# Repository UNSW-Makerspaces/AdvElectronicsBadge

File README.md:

# Arduino-Pico

Raspberry Pi Pico Arduino core, for all RP2040 boards

This is a port of the RP2040 (Raspberry Pi Pico processor) to the Arduino ecosystem. It uses the bare Raspberry Pi Pico SDK and a custom GCC 10.3/Newlib 4.0 toolchain.

# Documentation
See https://arduino-pico.readthedocs.io/en/latest/ along with the examples for more detailed usage information.

# Contributing
Read the [Contributing Guide](https://github.com/earlephilhower/arduino-pico/blob/master/docs/contrib.rst) for more information on submitting pull requests and porting libraries or sketches to this core.

# Supported Boards
* Raspberry Pi Pico
* Raspberry Pi Pico W
* UNSW Makerspaces PicoGamePad
* 0xCB Helios
* Adafruit Feather RP2040
* Adafruit Feather RP2040 SCORPIO
* Adafruit ItsyBitsy RP2040
* Adafruit KB2040
* Adafruit Macropad RP2040
* Adafruit QTPy RP2040
* Adafruit STEMMA Friend RP2040
* Adafruit Trinkey RP2040 QT
* Arduino Nano RP2040 Connect
* BridgeTek IDM2040-7A
* Cytron Maker Pi RP2040
* Cytron Maker Nano RP2040
* DatanoiseTV PicoADK+
* DeRuiLab FlyBoard2040 Core
* DFRobot Beetle RP2040
* ElectronicCats Hunter Cat NFC
* ExtremeElectronics RC2040
* Invector Labs Challenger RP2040 WiFi
* Invector Labs Challenger RP2040 WiFi/BLE
* Invector Labs Challenger NB RP2040 WiFi
* Invector Labs Challenger RP2040 LTE
* Invector Labs Challenger RP2040 LoRa
* Invector Labs Challenger RP2040 SubGHz
* Invector Labs Challenger RP2040 SD/RTC
* Invector Labs RPICO32
* Melopero Cookie RP2040
* Melopero Shake RP2040
* nullbits Bit-C PRO
* Pimoroni PGA2040
* Seeed XIAO RP2040
* Solder Party RP2040 Stamp
* SparkFun ProMicro RP2040
* SparkFun Thing Plus RP2040
* uPesy RP2040 DevKit
* VCC-GND YD-RP2040
* Viyalab Mizu RP2040
* Waveshare RP2040 Zero
* Waveshare RP2040 One
* Waveshare RP2040 Plus
* Waveshare RP2040 LCD 0.96
* Waveshare RP2040 LCD 1.28
* WIZnet W5100S-EVB-Pico
* WIZnet W5500-EVB-Pico
* WIZnet WizFi360-EVB-Pico
* Generic (configurable flash, I/O pins)

# Installing via Arduino Boards Manager
**Windows Users**: Please do not use the Windows Store version of the actual Arduino application
because it has issues detecting attached Pico boards.  Use the "Windows ZIP" or plain "Windows"
executable (EXE)  download direct from https://arduino.cc. and allow it to install any device
drivers it suggests.  Otherwise the Pico board may not be detected.  Also, if trying out the
2.0 beta Arduino please install the release 1.8 version beforehand to ensure needed device drivers
are present.  (See #20 for more details.)

Open up the Arduino IDE and go to File->Preferences.

In the dialog that pops up, enter the following URL in the "Additional Boards Manager URLs" field:

https://github.com/earlephilhower/arduino-pico/releases/download/global/package_rp2040_index.json

Hit OK to close the dialog.

Go to Tools->Boards->Board Manager in the IDE

Type "pico" in the search box and select "Add":

# Installing via GIT
To install via GIT (for latest and greatest versions):
````
mkdir -p ~/Arduino/hardware/pico
git clone https://github.com/earlephilhower/arduino-pico.git ~/Arduino/hardware/pico/rp2040
cd ~/Arduino/hardware/pico/rp2040
git submodule update --init
cd pico-sdk
git submodule update --init
cd ../tools
python3 ./get.py
`````

# Installing both Arduino and CMake
Tom's Hardware presented a very nice writeup on installing `arduino-pico` on both Windows and Linux, available at https://www.tomshardware.com/how-to/program-raspberry-pi-pico-with-arduino-ide

If you follow Les' step-by-step you will also have a fully functional `CMake`-based environment to build Pico apps on if you outgrow the Arduino ecosystem.

# Uploading Sketches
To upload your first sketch, you will need to hold the BOOTSEL button down while plugging in the Pico to your computer.
Then hit the upload button and the sketch should be transferred and start to run.

After the first upload, this should not be necessary as the `arduino-pico` core has auto-reset support.
Select the appropriate serial port shown in the Arduino Tools->Port->Serial Port menu once (this setting will stick and does not need to be
touched for multiple uploads).   This selection allows the auto-reset tool to identify the proper device to reset.
Them hit the upload button and your sketch should upload and run.

In some cases the Pico will encounter a hard hang and its USB port will not respond to the auto-reset request.  Should this happen, just
follow the initial procedure of holding the BOOTSEL button down while plugging in the Pico to enter the ROM bootloader.

# Uploading Filesystem Images
The onboard flash filesystem for the Pico, LittleFS, lets you upload a filesystem image from the sketch directory for your sketch to use.  Download the needed plugin from
* https://github.com/earlephilhower/arduino-pico-littlefs-plugin/releases

To install, follow the directions in
* https://github.com/earlephilhower/arduino-pico-littlefs-plugin/blob/master/README.md

For detailed usage information, please check the ESP8266 repo documentation (ignore SPIFFS related notes) available at
* https://arduino-esp8266.readthedocs.io/en/latest/filesystem.html

# Uploading Sketches with Picoprobe
If you have built a Raspberry Pi Picoprobe, you can use OpenOCD to handle your sketch uploads and for debugging with GDB.

Under Windows a local admin user should be able to access the Picoprobe port automatically, but under Linux `udev` must be told about the device and to allow normal users access.

To set up user-level access to Picoprobes on Ubuntu (and other OSes which use `udev`):
````
echo 'SUBSYSTEMS=="usb", ATTRS{idVendor}=="2e8a", ATTRS{idProduct}=="0004", GROUP="users", MODE="0666"' | sudo tee -a /etc/udev/rules.d/98-PicoProbe.rules
sudo udevadm control --reload
````

The first line creates a file with the USB vendor and ID of the Picoprobe and tells UDEV to give users full access to it.  The second causes `udev` to load this new rule.  Note that you will need to unplug and re-plug in your device the first time you create this file, to allow udev to make the device node properly.

Once Picoprobe permissions are set up properly, then select the board "Raspberry Pi Pico (Picoprobe)" in the Tools menu and upload as normal.

# Uploading Sketches with pico-debug
[pico-debug](https://github.com/majbthrd/pico-debug/) differs from Picoprobe in that pico-debug is a virtual debug pod that runs side-by-side on the same RP2040 that you run your code on; so, you only need one RP2040 board instead of two.  pico-debug also differs from Picoprobe in that pico-debug is standards-based; it uses the CMSIS-DAP protocol, which means even software not specially written for the Raspberry Pi Pico can support it.  pico-debug uses OpenOCD to handle your sketch uploads, and debugging can be accomplished with CMSIS-DAP capable debuggers including GDB.

Under Windows and macOS, any user should be able to access pico-debug automatically, but under Linux `udev` must be told about the device and to allow normal users access.

To set up user-level access to all CMSIS-DAP adapters on Ubuntu (and other OSes which use `udev`):
````
echo 'ATTRS{product}=="*CMSIS-DAP*", MODE="664", GROUP="plugdev"' | sudo tee -a /etc/udev/rules.d/98-CMSIS-DAP.rules
sudo udevadm control --reload
````

The first line creates a file that recognizes all CMSIS-DAP adapters and tells UDEV to give users full access to it.  The second causes `udev` to load this new rule.  Note that you will need to unplug and re-plug in your device the first time you create this file, to allow udev to make the device node properly.

Once CMSIS-DAP permissions are set up properly, then select the board "Raspberry Pi Pico (pico-debug)" in the Tools menu.

When first connecting the USB port to your PC, you must copy [pico-debug-gimmecache.uf2](https://github.com/majbthrd/pico-debug/releases/) to the Pi Pico to load pico-debug into RAM; after this, upload as normal.

# Debugging with Picoprobe/pico-debug, OpenOCD, and GDB
The installed tools include a version of OpenOCD (in the pqt-openocd directory) and GDB (in the pqt-gcc directory).  These may be used to run GDB in an interactive window as documented in the Pico Getting Started manuals from the Raspberry Pi Foundation.  For [pico-debug](https://github.com/majbthrd/pico-debug/), replace the raspberrypi-swd and picoprobe example OpenOCD arguments of "-f interface/raspberrypi-swd.cfg -f target/rp2040.cfg" or "-f interface/picoprobe.cfg -f target/rp2040.cfg" respectively in the Pico Getting Started manual with "-f board/pico-debug.cfg".

# Features
* Adafruit TinyUSB Arduino (USB mouse, keyboard, flash drive, generic HID, CDC Serial, MIDI, WebUSB, others)
* Bluetooth on the PicoW (Classic and BLE) with Keyboard, Mouse, Joystick, and Virtual Serial
* Generic Arduino USB Serial, Keyboard, Joystick, and Mouse emulation
* WiFi (Pico W)
* HTTP client and server (WebServer)
* SSL/TLS/HTTPS
* Over-the-Air (OTA) upgrades
* Filesystems (LittleFS and SD/SDFS)
* Multicore support (setup1() and loop1())
* FreeRTOS SMP support
* Overclocking and underclocking from the menus
* digitalWrite/Read, shiftIn/Out, tone, analogWrite(PWM)/Read, temperature
* Analog stereo audio in using DMA and the built-in ADC
* Analog stereo audio out using PWM hardware
* USB drive mode for data loggers (SingleFileDrive)
* Peripherals:  SPI master, Wire(I2C) master/slave, dual UART, emulated EEPROM, I2S audio input, I2S audio output, Servo
* printf (i.e. debug) output over USB serial

The RP2040 PIO state machines (SMs) are used to generate jitter-free:
* Servos
* Tones
* I2S Input
* I2S Output
* Software UARTs (Serial ports)

# Tutorials from Across the Web
Here are some links to coverage and additional tutorials for using `arduino-pico`
* The File:: class is taken from the ESP8266.  See https://arduino-esp8266.readthedocs.io/en/latest/filesystem.html
* Arduino Support for the Pi Pico available! And how fast is the Pico? - https://youtu.be/-XHh17cuH5E
* Pre-release Adafruit QT Py RP2040 - https://www.youtube.com/watch?v=sfC1msqXX0I
* Adafruit Feather RP2040 running LCD + TMP117 - https://www.youtube.com/watch?v=fKDeqZiIwHg
* Demonstration of Servos and I2C in Korean - https://cafe.naver.com/arduinoshield/1201
* Home Assistant Pico W integration starter project using Arduino - https://github.com/daniloc/PicoW_HomeAssistant_Starter
* Tutorials for the Raspberry Pi Pico / uPesy RP2040 DevKit board 
    - English version: https://www.upesy.com/blogs/tutorials/best-tutorials-for-rpi-pi-pico-with-arduino-code
    - French version: https://www.upesy.fr/blogs/tutorials/best-tutorials-for-rpi-pi-pico-with-arduino-code

# Contributing
If you want to contribute or have bugfixes, drop me a note at <earlephilhower@yahoo.com> or open an issue/PR here.

# Licensing and Credits
* The [Arduino IDE and ArduinoCore-API](https://arduino.cc) are developed and maintained by the Arduino team. The IDE is licensed under GPL.
* The [RP2040 GCC-based toolchain](https://github.com/earlephilhower/pico-quick-toolchain) is licensed under under the GPL.
* The [Pico-SDK](https://github.com/raspberrypi/pico-sdk) is by Raspberry Pi (Trading) Ltd and licensed under the BSD 3-Clause license.
* [Arduino-Pico](https://github.com/earlephilhower/arduino-pico) core files are licensed under the LGPL.
* [LittleFS](https://github.com/ARMmbed/littlefs) library written by ARM Limited and released under the [BSD 3-clause license](https://github.com/ARMmbed/littlefs/blob/master/LICENSE.md).
* [UF2CONV.PY](https://github.com/microsoft/uf2) is by Microsoft Corporation and licensed under the MIT license.
* Networking and filesystem code taken from the [ESP8266 Arduino Core](https://github.com/esp8266/Arduino) and licensed under the LGPL.
* DHCP server for AP host mode from the [Micropython Project](https://micropython.org), distributed under the MIT License.
* [FreeRTOS](https://freertos.org) is Copyright Amazon.com, Inc. or its affiliates, and distributed under the MIT license.
* [lwIP](https://savannah.nongnu.org/projects/lwip/) is (c) the Swedish Institute of Computer Science and licenced under the BSD license.
* [BearSSL](https://bearssl.org) library written by Thomas Pornin, is distributed under the [MIT License](https://bearssl.org/#legal-details).
* [UZLib](https://github.com/pfalcon/uzlib) is copyright (c) 2003 Joergen Ibsen and distributed under the zlib license.
* [LEAmDNS](https://github.com/LaborEtArs/ESP8266mDNS) is copyright multiple authors and distributed under the MIT license.
* [http-parser](https://github.com/nodejs/http-parser) is copyright Joyent, Inc. and other Node contributors.
* WebServer code modified from the [ESP32 WebServer](https://github.com/espressif/arduino-esp32/tree/master/libraries/WebServer) and is copyright (c) 2015 Ivan Grokhotkov and others

-Earle F. Philhower, III  
 earlephilhower@yahoo.com

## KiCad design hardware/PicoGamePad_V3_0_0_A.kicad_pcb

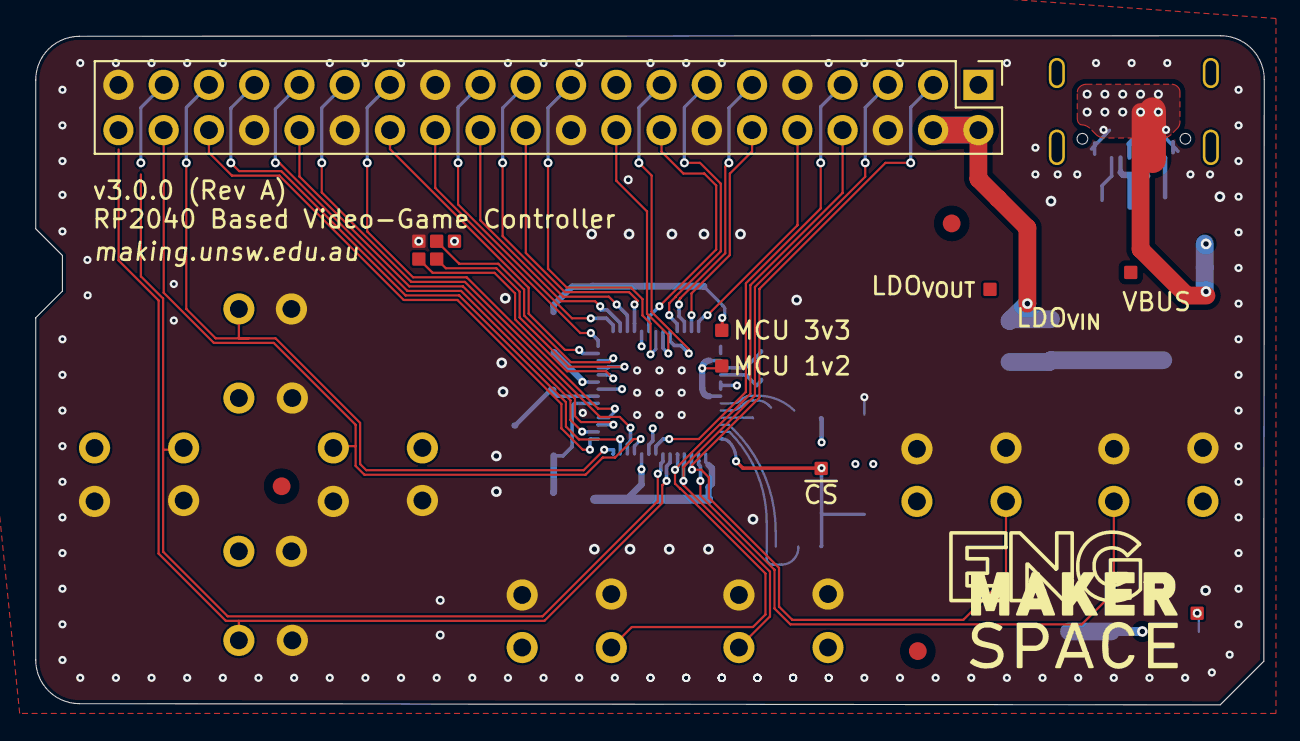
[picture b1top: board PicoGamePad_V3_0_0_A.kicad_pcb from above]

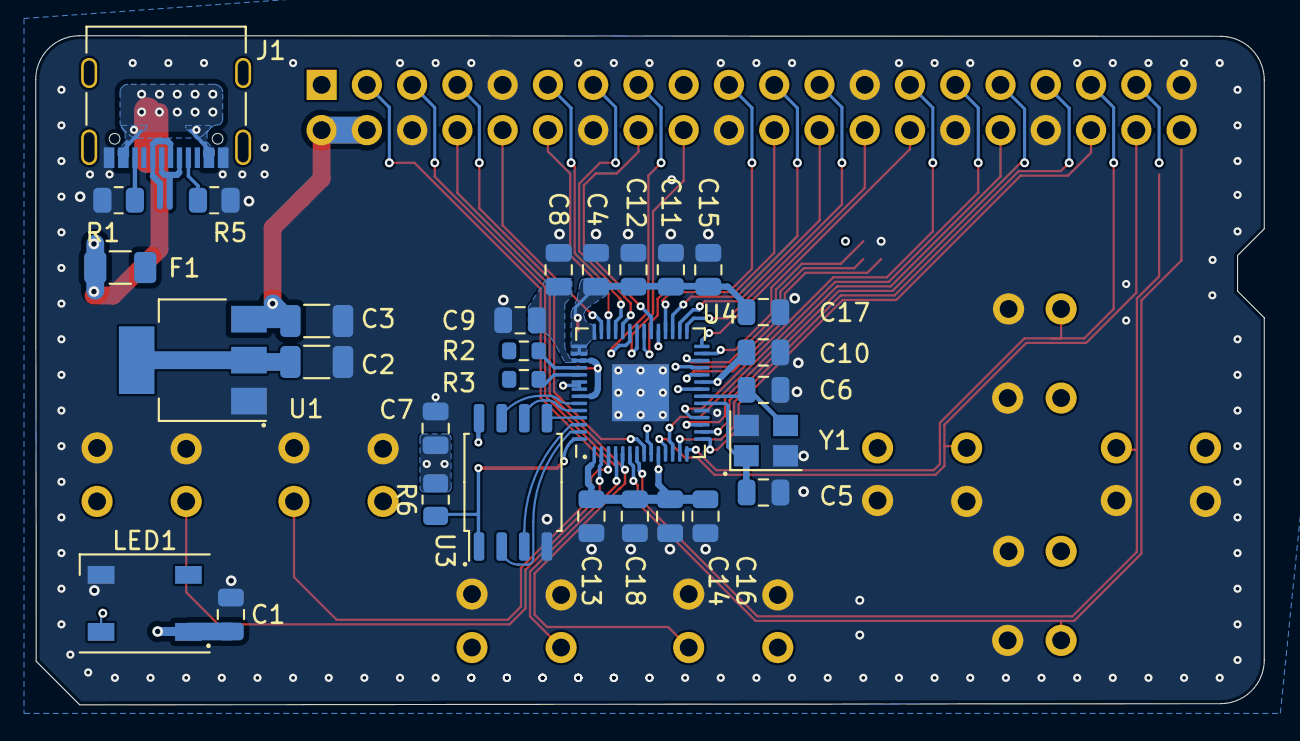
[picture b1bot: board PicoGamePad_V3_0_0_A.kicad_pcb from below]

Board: 4 copper layers, 68.9 x 37.6 mm, 54 parts (30 on the bottom side), 51 nets.

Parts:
C1, C4, C8, C11: 1μF; C_0805_2012Metric
C2, C3: 10μF; C_1206_3216Metric
C5, C6: 14pF; C_0805_2012Metric
C7, C9, C10, C12, C13, C14, C15, C16, C17, C18: 100nF; C_0805_2012Metric
F1: C261953; Fuse_1206_3216Metric
FID1: 0,1; Fiducial_1mm_Mask2mm
FID2: 0,0; Fiducial_1mm_Mask2mm
FID3: 1,0; Fiducial_1mm_Mask2mm
J1: C116159; USB_C_Receptacle_Palconn_UTC16-G
J3: RBP_GPIO_CONN; PinHeader_2x20_P2.54mm_Vertical
LED1: WS2812B; LED_WS2812B_PLCC4_5.0x5.0mm_P3.2mm
R1, R5: 5.1kΩ; R_0805_2012Metric
R2, R3: 27Ω; R_0603_1608Metric
R6: 10kΩ; R_0805_2012Metric
SW1, SW2, SW3, SW4, SW5, SW6, SW7, SW8: SW_Push; SW_TSC016XXXXXXX_4.5x3.0_H2.75
TP1: MCU 3v3; Testpoint_Custom
TP2: MCU 1v2; Testpoint_Custom
TP3: RUN; Testpoint_Custom
TP4: SWCLK; Testpoint_Custom
TP5: LED DATA; Testpoint_Custom
TP6: SWD; Testpoint_Custom
TP7: RUN_GND; Testpoint_Custom
TP8: VBUS; Testpoint_Custom
TP9: LDO_{VOUT}; Testpoint_Custom
TP10: LDO_{VIN}; Testpoint_Custom
TP11: SWD_3V3; Testpoint_Custom
TP12: ~{CS}; Testpoint_Custom
U1: ASM1117-3.3; SOT-223-3_TabPin2
U3: WQ25JVS; FLASH-SOIC-8
U4: RP2040; QFN-56-1EP_7x7mm_P0.4mm_EP3.2x3.2mm
Y1: X322512MMB4SI; Crystal_SMD_3225-4Pin_3.2x2.5mm

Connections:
+1V2: C8.1, C9.1, C10.1, TP2.1, U4.23 (DVDD), U4.45 (VREG_VOUT), U4.50 (DVDD)
+3V3: C3.1, C4.1, C7.1, C11.1, C12.1, C13.1, C14.1, C15.1, C16.1, C17.1, C18.1, J3.1, J3.17, R6.2, TP1.1, TP9.1, TP11.1, U1.2 (VO), U3.8 (VCC), U4.1 (IOVDD), U4.10 (IOVDD), U4.22 (IOVDD), U4.33 (IOVDD), U4.42 (IOVDD), U4.43 (ADC_AVDD), U4.44 (VREG_IN), U4.48 (USB_VDD), U4.49 (IOVDD)
/$.GPIO0: SW6.2, U4.2 (GPIO0)
/$.GPIO1: J3.3, SW4.2, U4.3 (GPIO1)
/$.GPIO2: J3.5, SW2.2, U4.4 (GPIO2)
/$.GPIO3: J3.8, SW8.2, U4.5 (GPIO3)
/$.GPIO4: J3.37, SW1.2, U4.6 (GPIO4)
/$.GPIO5: J3.40, SW3.2, U4.7 (GPIO5)
/$.GPIO6: J3.7, U4.8 (GPIO6)
/$.GPIO8: J3.38, SW7.2, U4.11 (GPIO8)
/$.GPIO9: J3.29, U4.12 (GPIO9)
/$.GPIO10: J3.33, U4.13 (GPIO10)
/$.GPIO11: J3.35, SW5.2, U4.14 (GPIO11)
/$.GPIO12: J3.36, U4.15 (GPIO12)
/$.GPIO13: J3.31, U4.16 (GPIO13)
/$.GPIO14: J3.32, U4.17 (GPIO14)
/$.GPIO15: J3.27, U4.18 (GPIO15)
/$.GPIO16: J3.28, U4.27 (GPIO16)
/$.GPIO17: J3.26, U4.28 (GPIO17)
/$.GPIO18: J3.23, U4.29 (GPIO18)
/$.GPIO19: J3.24, U4.30 (GPIO19)
/$.GPIO20: J3.21, U4.31 (GPIO20)
/$.GPIO21: J3.22, U4.32 (GPIO21)
/$.GPIO22: J3.16, U4.34 (GPIO22)
/$.GPIO23: J3.19, U4.35 (GPIO23)
/$.GPIO24: J3.18, U4.36 (GPIO24)
/$.GPIO25: J3.15, LED1.4 (DIN), TP5.1, U4.37 (GPIO25)
/$.GPIO26: J3.13, U4.38 (GPIO26_ADC0)
/$.GPIO27: J3.11, U4.39 (GPIO27_ADC1)
/$.GPIO28: J3.12, U4.40 (GPIO28_ADC2)
/$.GPIO29: J3.10, U4.41 (GPIO29_ADC3)
/D+: R3.2, U4.47 (USB_DP)
/D-: R2.2, U4.46 (USB_DM)
/SCK: U3.6 (CLK), U4.52 (QSPI_SCLK)
/SD0: U3.5 (DI(IO0)), U4.53 (QSPI_SD0)
/SD1: U3.2 (DO(IO1)), U4.55 (QSPI_SD1)
/SD2: U3.3 (IO2), U4.54 (QSPI_SD2)
/SD3: U3.7 (IO3), U4.51 (QSPI_SD3)
/USB_VBUS: F1.1, J1.A4 (VBUS), J1.A9 (VBUS), J1.B4 (VBUS), J1.B9 (VBUS)
/USB_{DATA}+: J1.A6 (D+), J1.B6 (D+), R3.1
/USB_{DATA}-: J1.A7 (D-), J1.B7 (D-), R2.1
/~CS: R6.1, TP12.1, U3.1 (~CS), U4.56 (QSPI_SS)
GND: C1.2, C2.2, C3.2, C4.2, C5.2, C6.2, C7.2, C8.2, C9.2, C10.2, C11.2, C12.2, C13.2, C14.2, C15.2, C16.2, C17.2, C18.2, J1.A1 (GND), J1.A12 (GND), J1.B1 (GND), J1.B12 (GND), J3.6, J3.9, J3.14, J3.20, J3.25, J3.30, J3.34, J3.39, LED1.3 (VSS), R1.2, R5.2, SW1.1, SW2.1, SW3.1, SW4.1, SW5.1, SW6.1, SW7.1, SW8.1, TP7.1, U1.1 (GND), U3.4 (GND), U4.19 (TESTEN), U4.57 (GND), Y1.2, Y1.4
unnamed: C5.1, U4.20 (XIN), Y1.1
unnamed: C6.1, U4.21 (XOUT), Y1.3
unnamed: J1.A5 (CC1), R5.1
unnamed: J1.B5 (CC2), R1.1
unnamed: TP3.1, U4.26 (RUN)
unnamed: TP4.1, U4.24 (SWCLK)
unnamed: TP6.1, U4.25 (SWD)
VBUS: C1.1, C2.1, F1.2, J3.2, J3.4, LED1.1 (VDD), TP8.1, TP10.1, U1.3 (VI)

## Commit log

2023-02-24 Pages
